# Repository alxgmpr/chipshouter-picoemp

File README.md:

# ChipSHOUTER-PicoEMP — Rev-2026

[![CC BY-SA 3.0][cc-by-sa-shield]][cc-by-sa]

A fork of [newaetech/chipshouter-picoemp](https://github.com/newaetech/chipshouter-picoemp)
adding **[`hardware/rev2026/`](hardware/rev2026/)** — a KiCad 10 port and rework
of the REV04 board. Upstream ships Altium sources and gerbers; this is an
editable KiCad project you can actually modify, with the design rules that matter
written down and enforced.

**[→ Rev-2026 documentation](hardware/rev2026/docs/)** &nbsp;·&nbsp;
[design notes](hardware/rev2026/docs/design-notes.md) &nbsp;·&nbsp;
[bring-up log](hardware/rev2026/docs/bringup.md) &nbsp;·&nbsp;
[open issues](hardware/rev2026/docs/open-issues.md) &nbsp;·&nbsp;
[fab outputs](hardware/rev2026/production/)

[Upstream's original README is preserved below.](#upstream-readme)

---

## What's different from REV04

* **Two upstream bugs fixed** — `R9` carried `R4`'s part data (75 Ω MPN on a 2 k
  part), and `C5` had no value.
* **A buffered trigger front-end** — a 74LVC1G17 Schmitt buffer with a series
  resistor and pulldown, plus an optional SMA input, instead of running the
  trigger straight into the Pico.
* **A bigger HV shield.** The 5.08 mm Phoenix terminal block is 13.80 mm tall and
  does not fit under upstream's 1551B half-shell, which gives 5.80 mm. This board
  uses an **inverted Hammond 1551G box** with 15.05 mm of clear height.
* **The 1 mm isolation barrier is enforced by a DRC rule** rather than by
  convention, with its reasoning and sources recorded in
  [`picoemp-rev2026.kicad_dru`](hardware/rev2026/picoemp-rev2026.kicad_dru).
* **All header footprints corrected** from 1.00/1.27 mm to 2.54 mm.

## Building one

1. **Boards** — upload
   [`hardware/rev2026/production/picoemp-rev2026-gerbers.zip`](hardware/rev2026/production/)
   to any fab. Two layers, 1.6 mm, 40.010 × 130.000 mm. The 1.6 mm thickness is
   required: the edge-mount SMA clamps the board edge and is specified for 0.062″.
2. **Parts** — [`production/bom.csv`](hardware/rev2026/production/) has MPNs,
   manufacturers and DigiKey part numbers for all 46 placed parts.
   [`bom/digikey-1board.txt`](hardware/rev2026/bom/) and `digikey-5boards.txt`
   are paste-ready DigiKey cart lists. **`R16` is DNP — do not fit it.**
3. **Shield** — Hammond 1551G, inverted, lid used as an underside cover on the
   same two #4 × ½″ screws. Trim `J4`'s pins to clear the lid's 3.05 mm recess.
4. **Firmware** — unchanged from upstream, in
   [`firmware/micropython/`](firmware/micropython/). This port does not modify it.
5. **Bring it up** — follow
   [`docs/bringup.md`](hardware/rev2026/docs/bringup.md), which is a real log
   from a real board rather than a checklist someone imagined.

**Read [`production/README.md`](hardware/rev2026/production/) and
[`docs/open-issues.md`](hardware/rev2026/docs/open-issues.md) before ordering.**
Nobody has fabbed from the current files yet — board #1 was built from an earlier
layout — and several known-imperfect items are not DRC violations, so no
automated check will catch them.

## Status

Both gates pass: 90 tests, and DRC reports 0 violations, 0 unconnected items and
0 schematic-parity issues. One board has been assembled and brought up: it
charges to roughly 261 V in about 2.1 seconds, asserts `CHARGED`, and discharges
on the button. **Pulsing has never been exercised** — there was no injection tip.

Two branches carry parked work that is not on `rev2026` and does not pass the
gates: [`feat/isolated-hv-sense`](../../tree/feat/isolated-hv-sense) (an AMC3336
block for calibrated isolated rail measurement) and
[`feat/hv-loop-return-plane`](../../tree/feat/hv-loop-return-plane) (a B.Cu
`HV_RTN` pour to cut discharge-loop inductance).

> ⚠️ **This is a high-voltage device.** It charges a capacitor to roughly 250 V,
> and the capacitor holds charge after power is removed. Everything in upstream's
> safety notes below applies to this board too — in particular, never operate it
> without the shield.

---

# Upstream README

Everything below is [NewAE's original README](https://github.com/newaetech/chipshouter-picoemp),
preserved unchanged. It describes the REV04 board that Rev-2026 is derived from,
and its safety guidance applies equally here.

The PicoEMP is a low-cost Electromagnetic Fault Injection (EMFI) tool, designed *specifically* for self-study and hobbiest research. Under the safety shield it looks like this:

You can see some details of the design in the [Intro Video](https://www.youtube.com/watch?v=nB5arJi-tVE).

## Thanks / Contributors

PicoEMP is a community-focused project, with major contributions from:
* Colin O'Flynn (original HW design, simple Python demo)
* [stacksmashing](https://twitter.com/ghidraninja) (C firmware for full PIO feature-set)
* [Lennert Wouters](https://twitter.com/LennertWo) (C improvements, first real demo)
* [@nilswiersma](https://github.com/nilswiersma) (Triggering/C improvements)

## Background

The [ChipSHOUTER](http://www.chipshouter.com) is a high-end Electromagnetic Fault Injection (EMFI) tool designed by Colin
at [NewAE Technology](http://www.newae.com). While not the first commercially available EMFI tool, ChipSHOUTER was the first
"easily purchasable" (even if expensive) tool with extensive open documentation. The tool was *not* open-source, but it
did contain a variety of detailed description of the design and architecture in the
[User Manual](https://github.com/newaetech/ChipSHOUTER/tree/master/documentation). The ChipSHOUTER design optimization focused in rough order on (1) safe operation, (2) high performance, (3) usability, and finally (4) cost. This results in a tool that covers many use-cases, but may be overkill (and too costly) for many. In additional, acquiring the safety testing/certification is not cheap, and must be accounted for in the product sale price.

The PicoEMP tries to fill in the gap that ChipSHOUTER leaves at the lower end of the spectrum. This PicoEMP project is *not* the
ChipSHOUTER. Instead it's designed to present a "bare bones" tool that has a design optimization focused in rough order of (1) safe
operation, (2) cost, (3) usability, (4) performance. Despite the focus on safety and low-cost, it works *suprisingly* well. It is also
*not* sold as a complete product - you are responsible for building it, ensuring it meets any relevant safety requirements/certifications,
and we completely disclaim all liability for what happens next. Please **only** use PicoEMP where you are building and controlling it
yourself, with total understanding of the operation and risks. It is *not* designed to be used in professional or educational environments,
where tools are expected to meet safety certifications (ChipSHOUTER was designed for these use-cases).

As an open-source project it also collects inputs from various community members, and welcomes your contributions! It also has various remixes of it, including:

* TODO link to people's remixes.

## Building a PicoEMP

The PicoEMP uses a Raspberry Pi Pico as the controller, inspired by @nezza using it for the debug-n-dump tool. You could alternatively use an Arduino or another microcontroller. You basically just need a few things:

1. PWM output to drive HV transformer.
2. Pulse pin to generate a pulse.
3. Status pin to monitor the HV status.

You have two options for building the PicoEMP: (1) total scratch build, or (2) easy-assemble build.

### Scratch Build

The PCB is *mostly* one layer. Original versions of it were milled on a Bantam PCB mill, and the final 'production' version is designed
to still allow this simple milling process. You can find details in the [gerbers](hardware/gerbers) folder, including Bantam-optimized files
which remove some of the smaller vias (used for the mounting holes), and require you to surface-mount the Raspberry Pi Pico. Here was
'rev3' of the PCB with a few hacked up tests:

If you've got time you can order the "real" PCBs from the [gerbers](hardware/gerbers) as well.

The BOM and build details are described in the [hardware](hardware) folder. If you cannot find the plastic shield (the upper half of Hammond
1551BTRD is used), you can find a simple 3D-printable shield as well. The official shield is low-cost and available from Digikey/Mouser/
Newark so you can purchase alongside everything else you need.

**IMPORTANT**: The plastic shield is critical for safe operation. While the output itself is isolated from the input connections, you will still **easily shock yourself** on the exposed high-voltage capacitor and circuitry. **NEVER** operate the device without the shield.

### Easy-Assemble Build

The Easy-Assembly build uses a "mostly complete" SMD board, which you need to solder a Raspberry Pi Pico, switches, and through-hole headers. Currently it's available only on the [NewAE Store](https://store.newae.com/chipshouter-picoemp). We're working to
get this listed on Mouser for much cheaper worldwide shipping (the NewAE store doesn't get great rates & due to issues with Canada's postal system for international shipments quotes mostly via DHL).

### Programming the PicoEMP

You'll need to program the PicoEMP with the firmware in the [firmware](firmware) directory. You can run other tasks on the microcontroller
as well.

### Building the EM Injection Tip (Probe / Coil)

You will also need an "injection tip", typically made with a ferrite core and some wires wrapped around it. You can see examples of such cores in the ChipSHOUTER kit. The following shows a few homemade & commercial tips:

You can make your own from suitable SMA connectors, magnet wire, and a ferrite core material. See the [injection_tips](hardware/injection_tips)
folder for more examples and details on building the probes.

*Reader Note: Please submit your own examples with a pull-request to this repo, it would be great to have more examples of probe geometries*

You can find additional examples of homemade cores in research papers such as:

* A. Cui, R. Housley, "BADFET: Defeating Modern Secure Boot Using Second-Order Pulsed Electromagnetic Fault Injection," USENIX Workshop on Offensive Technologies (WOOT 17), 2017.  [Paper Link.](https://www.usenix.org/conference/woot17/workshop-program/presentation/cui) [Slides Link.](https://github.com/RedBalloonShenanigans/BADFET)
* J. Balasch, D. Arumí and S. Manich, "Design and validation of a platform for electromagnetic fault injection," 2017 32nd Conference on Design of Circuits and Integrated Systems (DCIS), 2017, pp. 1-6. [Paper Link.](https://upcommons.upc.edu/bitstream/handle/2117/116688/bare_conf.pdf)
* J. Toulemont, G. Chancel, J. M. Galliere, F. Mailly, P. Nouet and P. Maurine, "On the scaling of EMFI probes," 2021 Workshop on Fault Detection and Tolerance in Cryptography (FDTC), 2021. [Paper Link.](https://ieeexplore.ieee.org/abstract/document/9565575) [Slides Link.](https://jaif.io/2021/media/JAIF2021%20-%20Toulemont.pdf)
* LimitedResults. "Enter the Gecko," 2021. [Blog Link](https://limitedresults.com/2021/06/enter-the-efm32-gecko/)
* C. Gaine, J-P. Nikolovski, D. Aboulkassimi, J-M. Dutertre. "New probe design for hardware characterization by ElectroMagnetic Fault Injection," EMC Europe 2022 [Paper Link.] (https://hal-cea.archives-ouvertes.fr/cea-03657852/file/article_archivesouvertes.pdf)
* 
### Useful References

If you don't know where to start with FI, you may find a couple chapters of the [Hardware Hacking Handbook](https://nostarch.com/hardwarehacking) useful.

You can see a demo of PicoEMP being used on a real attack in this [TI CC SimpleLink attack demo](https://github.com/KULeuven-COSIC/SimpleLink-FI/blob/main/notebooks/5_ChipSHOUTER-PicoEMP.ipynb).

## Using the PicoEMP

The general usage of the PicoEMP is as follows:

1. Press the "ARM" button. The red "ARMING" led will come on instantly telling you it's trying to charge the high voltage.
2. The red "HV" led will come on after a few seconds saying it is charged to "some voltage".
3. Place the probe tip overtop of the target.
4. Press the "Pulse" button.

You can see more examples of this in the [Intro Video](https://www.youtube.com/watch?v=nB5arJi-tVE).

You can even use the Raspberry Pi Pico to attack a Raspberry Pi "regular"! Here's a demo hitting a RSA signature on a Raspberry Pi (the demo code taken from Colin's [Remoticon 2021 Talk](https://github.com/colinoflynn/remoticon-2021-levelup-hardware-hacking/tree/master/rpi-glitching)):

**WARNING**: The high voltage will be applied across the SMA connector. If an injection tip (coil) is present, it will absorb most of the power. If you leave the SMA connector open, you will present a high voltage pulse across this SMA and could shock yourself. Do NOT touch the output SMA tip as a general "best practice", and treat the output as if it has a high voltage present.

The full ChipSHOUTER detects the missing connector tip and refuses to power up the high voltage, the PicoEMP does not have this failsafe!

## About the High Voltage Isolation

Most EMFI tools generate high voltages (similar to a camera flash). Many previous designs of open-source EMFI tools would work well, but [exposed the user to high voltages](https://github.com/RedBalloonShenanigans/BADFET). This was fine provided you use the tool correctly, but of course there is always a risk of grabbing the electrically "hot" tool! This common design choice happens because the easiest way to design an EMFI tool is with "low-side switching" (there is a very short mention of these design choices as well in my [book](https://www.nostarch.com/hardwarehacking) if you are curious). With low-side switching the output connector is always "hot", which presents a serious shock hazard.

PicoEMP gets around this problem by floating the high-voltage side, meaning there is no electrical path between the EMFI probe output and the input voltage ground. With the isolated high voltage output we can use the simple "low-side switching" in a safe manner. Some current will still flow due to the high-frequency spikes, so this isn't *perfect*, but it works well enough in practice (well enough you will shock yourself less often).

The caveat here is for this to work you also need to isolate your gate drive. There are a variety of [solutions to this](https://www.analog.com/en/technical-articles/powering-the-isolated-side-of-your-half-bridge-configuration.html), with the simplist being a gate drive transformer (GDT). The PicoEMP uses the transformer architecture, with some simplifications to further reduce BOM count.

More details of the design are available in the [hardware](hardware) folder.

### Hipot Testing for Validating Isolation

Easy-assemble builds have been subject to a hipot test. This test validates the isolation exists, and has not been compromised by things like leftover flux on the PCB.

This test applies a high voltage (1000V) from the SMA connector pads to the low-voltage signals shorted together. The test is done at 1000V DC, with test passing if LESS than 1 uA of current flows over the 60 seconds test duration. Note this limits is *far* lower than most industry standard limits.

### Technical Differences between ChipSHOUTER and PicoEMP

The main differences from a technical standpoint:

* ChipSHOUTER uses a much more powerful high voltage circuit and transformer (up to ~30W vs ~0.2W) that gives it
  almost unlimited glitch delivery, typically limited by your probe tip. The PicoEMP is slower to recover, typically ~1 to 4 seconds between
  glitches.

* ChipSHOUTER has a larger internal energy storage & more powerful output drivers.

* ChipSHOUTER has a controlled high-voltage setting from 150V to 500V. PicoEMP generates ~250V, there is some feedback but it's uncalibrated.
  **NOTE**: The PicoEMP allows some control of output pulse size by instead controlling the drive signal. This is less reliable (more variability
  in the output), but meets the goal of using the lowest-cost control method.

## License

This work is licensed under a [Creative Commons Attribution-ShareAlike 3.0 International License][cc-by-sa].

[cc-by-sa]: http://creativecommons.org/licenses/by-sa/3.0/
[cc-by-sa-image]: https://licensebuttons.net/l/by-sa/3.0/88x31.png
[cc-by-sa-shield]: https://img.shields.io/badge/License-CC%20BY--SA%203.0-lightgrey.svg

ChipSHOUTER is a trademark of NewAE Technology Inc., registered in the US, European Union, and other jurisdictions.
PicoEMP is a trademark of NewAE Technology Inc.

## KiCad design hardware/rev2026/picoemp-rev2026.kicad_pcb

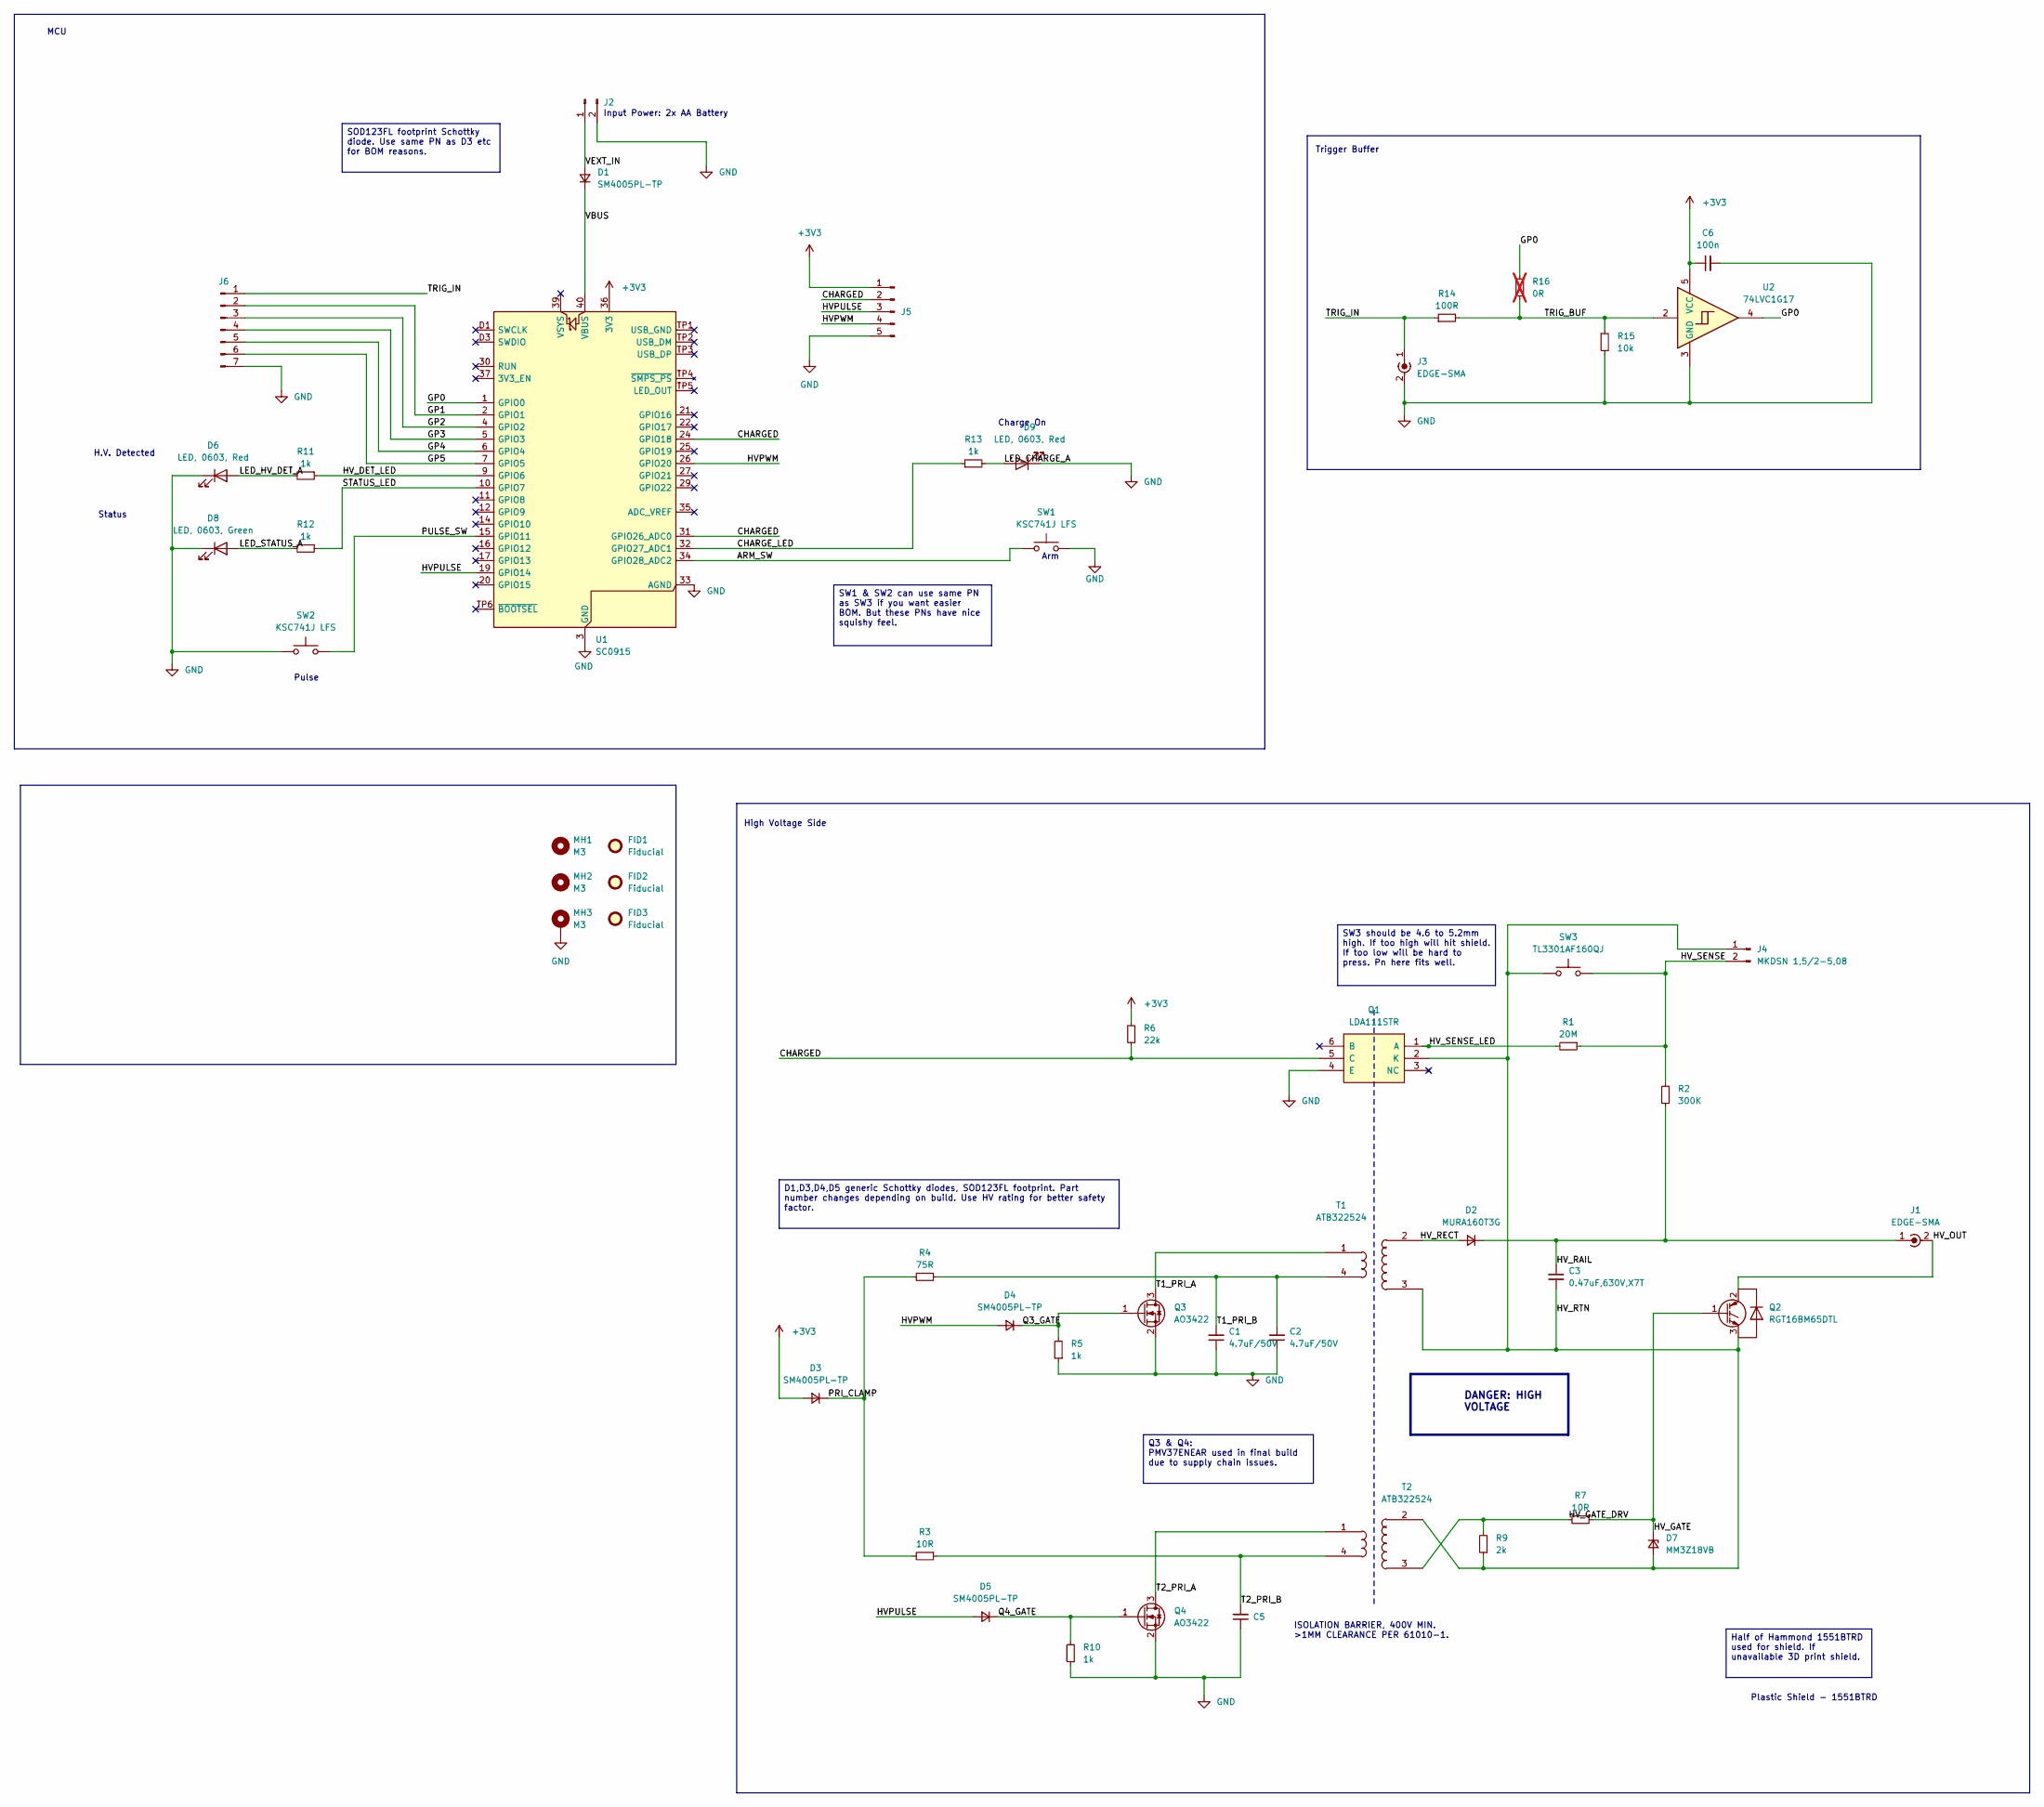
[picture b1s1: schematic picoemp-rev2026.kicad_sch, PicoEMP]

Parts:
C1, C2: 4.7uF/50V; C_0805_2012Metric; MPN C2012X5R1H475K125AB; DigiKey 445-5980-1-ND
C3: 0.47uF,630V,X7T; C_2220_5750Metric; MPN GR355DD7LQ474KW01K; DigiKey 490-GR355DD7LQ474KW01KCT-ND
C5, C6: 100n; C_0603_1608Metric; MPN C0603C104K5RACTU; DigiKey 399-5089-2-ND
D1, D3, D4, D5: SM4005PL-TP; D_SOD-123FL; MPN SM4005PL-TP; DigiKey SM4005PL-TPMSCT-ND
D2: MURA160T3G; D_SMA; MPN MURA160T3G
D6, D9: LED, 0603, Red; LED_0603_1608Metric; MPN APT1608SURCK; DigiKey 754-1123-1-ND
D7: MM3Z18VB; D_SOD-323F; MPN MM3Z18VB; DigiKey MM3Z18VBCT-ND
D8: LED, 0603, Green; LED_0603_1608Metric; MPN APT1608CGCK; DigiKey 754-1116-1-ND
FID1, FID2, FID3: Fiducial; Fiducial_0.5mm_Mask1.5mm
J1, J3: EDGE-SMA; SMA_Linx_CONSMA020_062_G_EdgeMount; MPN CONSMA020.062-G; DigiKey 343-CONSMA020.062-G-ND
J2: 1x2_Pin_Header; JST_XH_S2B-XH-A_1x02_P2.50mm_Horizontal; MPN S2B-XH-A(LF)(SN); DigiKey 455-2257-ND
J4: MKDSN 1,5/2-5,08; TerminalBlock_Phoenix_MKDSN-1,5-2-5.08_1x02_P5.08mm_Horizon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; MPN 1548128
J5: Header 5; PinHeader_1x05_P2.54mm_Vertical
J6: Header 7; PinHeader_1x07_P2.54mm_Vertical
MH1, MH2: M3; MountingHole_3.2mm_M3
MH3: M3; MountingHole_3.2mm_M3_Pad_Via
Q1: LDA111STR; SOP-6_LDA111; MPN LDA111STR; DigiKey 212-LDA111SCT-ND
Q2: RGT16BM65DTL; TO-252-3_TabPin2; MPN RGT16BM65DTL
Q3, Q4: AO3422; SOT-23; MPN AO3422
R1: 20M; R_2010_5025Metric; MPN CRMA2010AF20M0FKEF
R2: 300K; R_2512_6332Metric; MPN 3522300KFT; DigiKey A121215CT-ND
R3, R7: 10R; R_0603_1608Metric; MPN RC0603FR-0710RL; DigiKey 311-10.0HRCT-ND
R4: 75R; R_0805_2012Metric; MPN RC0805FR-0775RL; DigiKey 311-75.0CRCT-ND
R5, R10, R11, R12, R13: 1k; R_0603_1608Metric; MPN RC0603FR-071KL; DigiKey 311-1.00KHRCT-ND
R6: 22k; R_0603_1608Metric; MPN RC0603FR-0722KL; DigiKey 311-22.0KHRCT-ND
R9: 2k; R_0805_2012Metric; MPN RC0805FR-072KL; DigiKey 311-2.00KCRCT-ND
R14: 100R; R_0603_1608Metric; MPN RC0603FR-07100RL; DigiKey 311-100HRCT-ND
R15: 10k; R_0603_1608Metric; MPN RC0603FR-0710KL; DigiKey 311-10.0KHRCT-ND
R16: 0R; R_0603_1608Metric; MPN RC0603JR-070RL; DigiKey 311-0.0GRCT-ND; not fitted
SW1, SW2: KSC741J LFS; SW_Push_1P1T_NO_CK_KSC7xxJ; MPN KSC741JLFS; DigiKey CKN10309CT-ND
SW3: TL3301AF160QJ; SW_Push_ESwitch_TL3301AJ; MPN TL3301AF160QJ; DigiKey EG4374CT-ND
T1, T2: ATB322524; MPN ATB322524-0110-T000; DigiKey 445-8636-1-ND
U1: SC0915; RaspberryPi_Pico_SMD; MPN SC0915
U2: 74LVC1G17; SOT-23-5; MPN 74LVC1G17GV,125; DigiKey 1727-6070-1-ND

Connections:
+3V3: C6.1, D3.2 (A), J5.1, R6.2, U1.36 (3V3), U2.5 (VCC)
/ARM_SW: SW1.1, U1.34 (GPIO28_ADC2)
/CHARGED: J5.2, Q1.5 (C), R6.1, U1.24 (GPIO18), U1.31 (GPIO26_ADC0)
/CHARGE_LED: R13.1, U1.32 (GPIO27_ADC1)
/GP0: R16.1, U1.1 (GPIO0), U2.4
/GP1: J6.2, U1.2 (GPIO1)
/GP2: J6.3, U1.4 (GPIO2)
/GP3: J6.4, U1.5 (GPIO3)
/GP4: J6.5, U1.6 (GPIO4)
/GP5: J6.6, U1.7 (GPIO5)
/HVPULSE: D5.2 (A), J5.3, U1.19 (GPIO14)
/HVPWM: D4.2 (A), J5.4, U1.26 (GPIO20)
/HV_DET_LED: R11.1, U1.9 (GPIO6)
/HV_GATE: D7.1 (K), Q2.1 (G), R7.1
/HV_GATE_DRV: R7.2, R9.2, T2.3
/HV_OUT: J1.2 (Ext), Q2.2 (C)
/HV_RAIL: C3.2, D2.1 (K), J1.1 (In), R2.1
/HV_RECT: D2.2 (A), T1.2
/HV_RTN: C3.1, D7.2 (A), J4.1, Q1.2 (K), Q2.3 (E), R9.1, SW3.1, T1.3, T2.2
/HV_SENSE: J4.2, R1.1, R2.2, SW3.2
/HV_SENSE_LED: Q1.1 (A), R1.2
/LED_CHARGE_A: D9.2 (A), R13.2
/LED_HV_DET_A: D6.2 (A), R11.2
/LED_STATUS_A: D8.2 (A), R12.2
/PRI_CLAMP: D3.1 (K), R3.2, R4.2
/PULSE_SW: SW2.1, U1.15 (GPIO11)
/Q3_GATE: D4.1 (K), Q3.1 (G), R5.2
/Q4_GATE: D5.1 (K), Q4.1 (G), R10.2
/STATUS_LED: R12.1, U1.10 (GPIO7)
/T1_PRI_A: Q3.3 (D), T1.1
/T1_PRI_B: C1.2, C2.2, R4.1, T1.4
/T2_PRI_A: Q4.3 (D), T2.1
/T2_PRI_B: C5.2, R3.1, T2.4
/TRIG_BUF: R14.2, R15.1, R16.2, U2.2
/TRIG_IN: J3.1 (In), J6.1, R14.1
/VBUS: D1.1 (K), U1.40 (VBUS)
/VEXT_IN: D1.2 (A), J2.1
GND: C1.1, C2.1, C5.1, C6.2, D6.1 (K), D8.1 (K), D9.1 (K), J2.2, J3.2 (Ext), J5.5, J6.7, MH3.1 (1_1), Q1.4 (E), Q3.2 (S), Q4.2 (S), R5.1, R10.1, R15.2, SW1.2, SW2.2, U1.3 (GND), U1.8 (GND), U1.13 (GND), U1.18 (GND), U1.23 (GND), U1.28 (GND), U1.33 (AGND), U1.38 (GND), U1.D2 (GND), U2.3 (GND)

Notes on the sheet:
MCU
High Voltage Side
Plastic Shield - 1551BTRD‎
Pulse
Charge On
H.V. Detected
Arm
Input Power: 2x AA Battery
Trigger Buffer
ISOLATION BARRIER, 400V MIN. >1MM CLEARANCE PER 61010-1.
Q3 & Q4: PMV37ENEAR used in final build due to supply chain issues.
SW3 should be 4.6 to 5.2mm high. If too high will hit shield. If too low will be hard to press. Pn here fits well.
Half of Hammond 1551BTRD used for shield. If unavailable 3D print shield.
Status
SOD123FL footprint Schottky diode. Use same PN as D3 etc for BOM reasons.
SW1 & SW2 can use same PN as SW3 if you want easier BOM. But these PNs have nice squishy feel.
DANGER: HIGH VOLTAGE
D1,D3,D4,D5 generic Schottky diodes, SOD123FL footprint. Part number changes depending on build. Use HV rating for better safety factor.

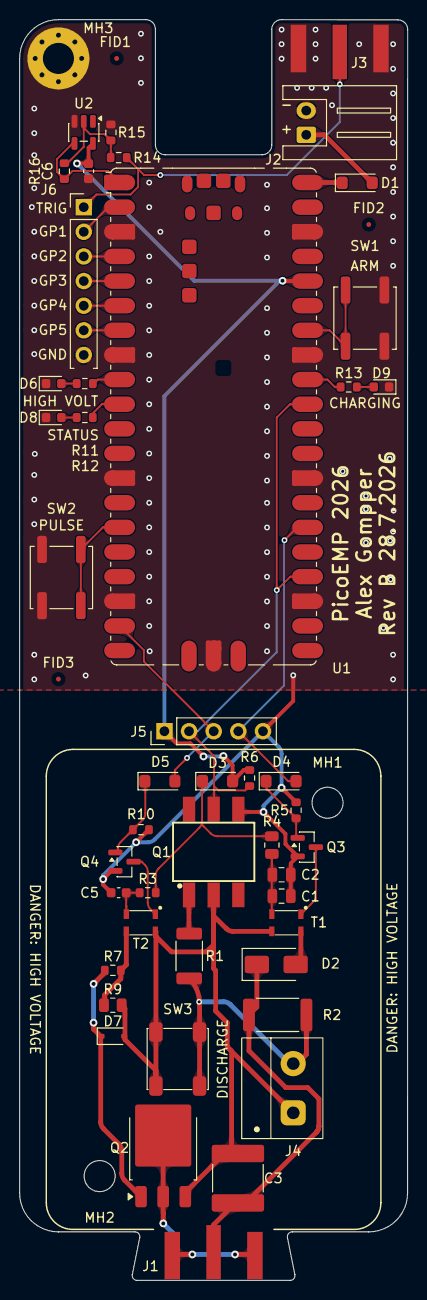
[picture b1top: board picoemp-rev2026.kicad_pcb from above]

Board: 2 copper layers, 40.0 x 130.0 mm, 52 parts (0 on the bottom side), 38 nets.

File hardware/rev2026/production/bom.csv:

"Refs","Value","Footprint","MPN","Manufacturer","DigiKey","DNP","Qty"
"C1,C2","4.7uF/50V","Capacitor_SMD:C_0805_2012Metric","C2012X5R1H475K125AB","TDK","445-5980-1-ND","","2"
"C3","0.47uF,630V,X7T","Capacitor_SMD:C_2220_5750Metric","GR355DD7LQ474KW01K","Murata Electronics","490-GR355DD7LQ474KW01KCT-ND","","1"
"C5,C6","100n","Capacitor_SMD:C_0603_1608Metric","C0603C104K5RACTU","KEMET","399-5089-2-ND","","2"
"D1,D3-D5","SM4005PL-TP","picoemp:D_SOD-123FL","SM4005PL-TP","MCC","SM4005PL-TPMSCT-ND","","4"
"D2","MURA160T3G","Diode_SMD:D_SMA","MURA160T3G","onsemi","","","1"
"D6,D9","LED, 0603, Red","LED_SMD:LED_0603_1608Metric","APT1608SURCK","Kingbright","754-1123-1-ND","","2"
"D7","MM3Z18VB","Diode_SMD:D_SOD-323F","MM3Z18VB","onsemi","MM3Z18VBCT-ND","","1"
"D8","LED, 0603, Green","LED_SMD:LED_0603_1608Metric","APT1608CGCK","Kingbright","754-1116-1-ND","","1"
"J1,J3","EDGE-SMA","picoemp:SMA_Linx_CONSMA020_062_G_EdgeMount","CONSMA020.062-G","TE Connectivity Linx","343-CONSMA020.062-G-ND","","2"
"J2","1x2_Pin_Header","Connector_JST:JST_XH_S2B-XH-A_1x02_P2.50mm_Horizontal","S2B-XH-A(LF)(SN)","JST","455-2257-ND","","1"
"J4","MKDSN 1,5/2-5,08","picoemp:TerminalBlock_Phoenix_MKDSN-1,5-2-5.08_1x02_P5.08mm_Horizontal","1548128","Phoenix Contact","","","1"
"J5","Header 5","Connector_PinHeader_2.54mm:PinHeader_1x05_P2.54mm_Vertical","","","","","1"
"J6","Header 7","Connector_PinHeader_2.54mm:PinHeader_1x07_P2.54mm_Vertical","","","","","1"
"Q1","LDA111STR","picoemp:SOP-6_LDA111","LDA111STR","IXYS SEMICONDUCTOR","212-LDA111SCT-ND","","1"
"Q2","RGT16BM65DTL","Package_TO_SOT_SMD:TO-252-3_TabPin2","RGT16BM65DTL","ROHM","","","1"
"Q3,Q4","AO3422","Package_TO_SOT_SMD:SOT-23","AO3422","Alpha & Omega Semiconductor","","","2"
"R1","20M","Resistor_SMD:R_2010_5025Metric","CRMA2010AF20M0FKEF","Vishay","","","1"
"R2","300K","Resistor_SMD:R_2512_6332Metric","3522300KFT","TE Connectivity","A121215CT-ND","","1"
"R3,R7","10R","Resistor_SMD:R_0603_1608Metric","RC0603FR-0710RL","Yageo","311-10.0HRCT-ND","","2"
"R4","75R","Resistor_SMD:R_0805_2012Metric","RC0805FR-0775RL","Yageo","311-75.0CRCT-ND","","1"
"R5,R10-R13","1k","Resistor_SMD:R_0603_1608Metric","RC0603FR-071KL","Yageo","311-1.00KHRCT-ND","","5"
"R6","22k","Resistor_SMD:R_0603_1608Metric","RC0603FR-0722KL","Yageo","311-22.0KHRCT-ND","","1"
"R9","2k","Resistor_SMD:R_0805_2012Metric","RC0805FR-072KL","Yageo","311-2.00KCRCT-ND","","1"
"R14","100R","Resistor_SMD:R_0603_1608Metric","RC0603FR-07100RL","Yageo","311-100HRCT-ND","","1"
"R15","10k","Resistor_SMD:R_0603_1608Metric","RC0603FR-0710KL","Yageo","311-10.0KHRCT-ND","","1"
"R16","0R","Resistor_SMD:R_0603_1608Metric","RC0603JR-070RL","Yageo","311-0.0GRCT-ND","DNP","1"
"SW1,SW2","KSC741J LFS","Button_Switch_SMD:SW_Push_1P1T_NO_CK_KSC7xxJ","KSC741JLFS","C&K","CKN10309CT-ND","","2"
"SW3","TL3301AF160QJ","picoemp:SW_Push_ESwitch_TL3301AJ","TL3301AF160QJ","E-Switch","EG4374CT-ND","","1"
"T1,T2","ATB322524","picoemp:ATB322524","ATB322524-0110-T000","TDK","445-8636-1-ND","","2"
"U1","SC0915","Module:RaspberryPi_Pico_SMD","SC0915","Raspberry Pi","","","1"
"U2","74LVC1G17","Package_TO_SOT_SMD:SOT-23-5","74LVC1G17GV,125","Nexperia","1727-6070-1-ND","","1"

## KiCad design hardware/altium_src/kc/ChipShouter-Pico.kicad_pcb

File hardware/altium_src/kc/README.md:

# ⚠️ Incomplete REV04 → KiCad migration — do not use as a reference

This directory is an **abandoned, in-progress** import of the upstream REV04
Altium design into KiCad. It is kept for history only.

**It has at least one known wiring error.** In the HV sense section, `R1`'s
lower lead lands on `HV_RTN` and `Q1` pin 1 floats, because the Altium import
flattened a wire hop into a junction. The sense chain is therefore wrong.

Its `audit/AUDIT.md` §4b also states the sense chain as "HV → R1 → Q1 LED → R2 →
GND". That is wrong too — the real order puts `R2` first.

## Where to look instead

| For | Use |
|---|---|
| **Ground truth on circuit topology** | [`../../SCH-PICOEMP-REV04.PDF`](../../SCH-PICOEMP-REV04.PDF) |
| A working KiCad version of this board | [`../../rev2026/`](../../rev2026/) |
| The original Altium sources | [`../`](../) |

The correct sense chain is:

```
HV_RAIL → R2 (300K) → HV_SENSE → R1 (20M) → Q1 LED → HV_RTN
```

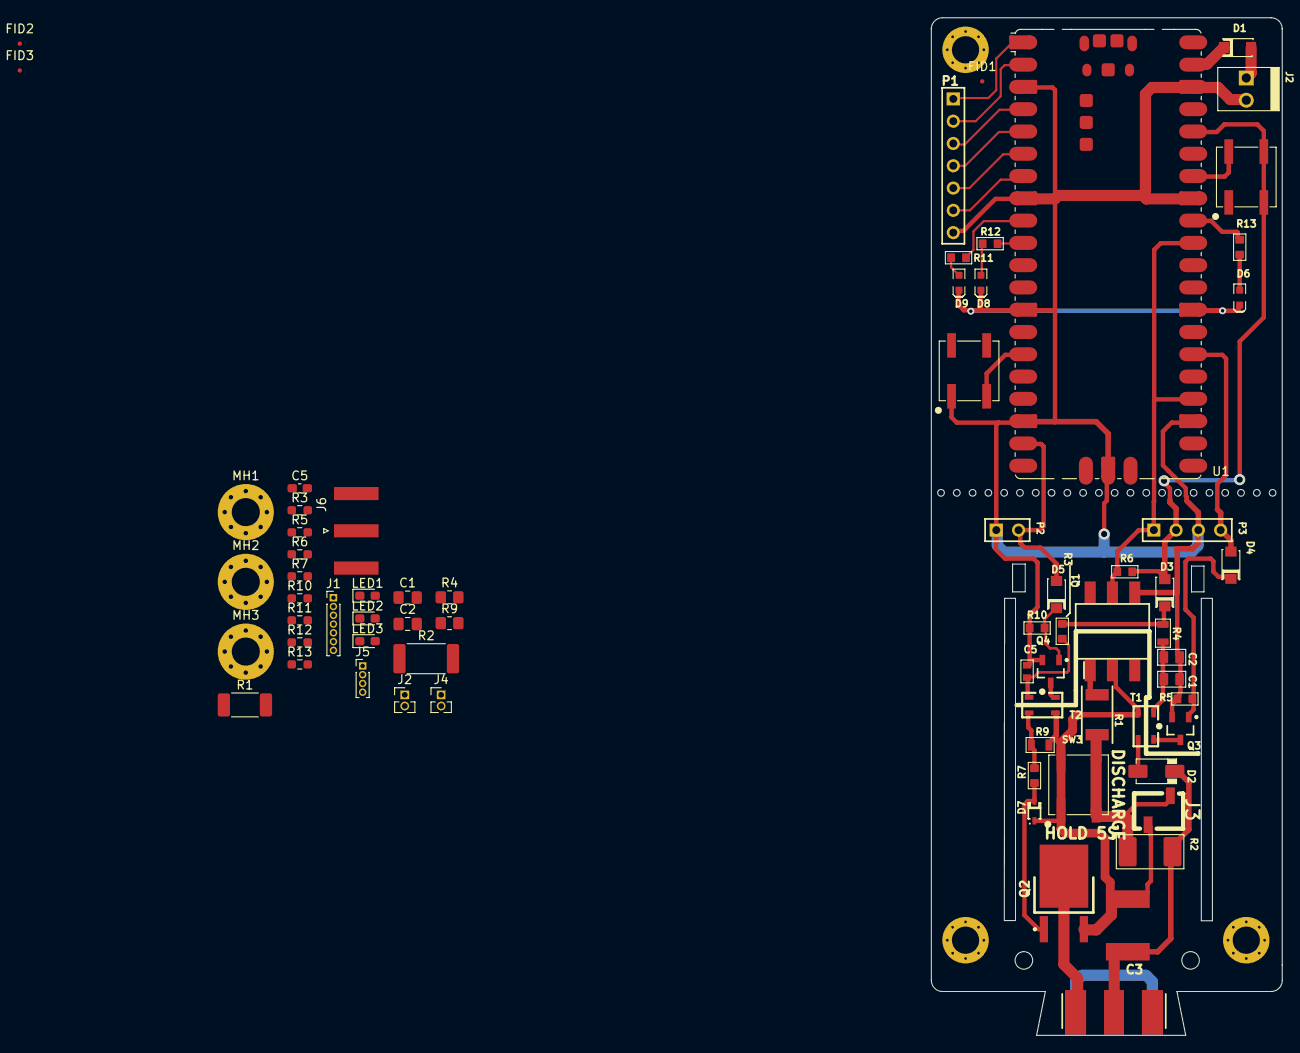
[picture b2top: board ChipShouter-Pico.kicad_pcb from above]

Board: 2 copper layers, 40.0 x 116.0 mm, 73 parts (0 on the bottom side), 47 nets.

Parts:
C1, C2: 4.7uF/50V; C_0805_2012Metric_Pad1.18x1.45mm_HandSolder
C1#2, C2#2: 4.7uF/50V; CAPC0805_M
C3: 0.47uF,630V,X7T; CKG57N_2220
C5: ${ALTIUM_VALUE}; C_0603_1608Metric_Pad1.08x0.95mm_HandSolder
C5#2: 100n; CAPC0603_M
D1, D3, D4, D5: DSS13UTR
D2: MURA160T3G; DO-214AC
D6, D9: LED, 0603, Red; LED-0603-RED
D7: MM3Z18VB; SOD323
D8: LED, 0603, Green; LED-0603-GREEN
FID1, FID2, FID3: Fiducial; Fiducial_0.5mm_Mask1.5mm
J1: Header 7; PinHeader_1x07_P1.00mm_Vertical
J1#2: EDGE-SMA; CON-SMA-MALE-PCB-EDGE062
J2: 1x2_Pin_Header; PinHeader_1x02_P1.27mm_Vertical
J2#2: 1x2_Pin_Header; 22-23-2021
J3: BG306-02-A-2-0400-L-G; BG306-R2-2PIN
J4: Header 2; PinHeader_1x02_P1.27mm_Vertical
J5: Header 4; PinHeader_1x04_P1.00mm_Vertical
J6: EDGE-SMA; SMA_Amphenol_132289_EdgeMount
LED1, LED3: LED, 0603, Red; LED_0603_1608Metric_Pad1.05x0.95mm_HandSolder
LED2: LED, 0603, Green; LED_0603_1608Metric_Pad1.05x0.95mm_HandSolder
MH1, MH2, MH3#2: M3; MountingHole_3.2mm_M3_Pad_Via
MH1#2, MH2#2, MH3: M3, Tight Fit; MOUNT_M3_TIGHT
P1: Header 7; HDR1X7
P2: Header 2; HDR1X2
P3: Header 4; HDR1X4
Q1: LDA111STR; SOP254P952X470-6N
Q2: RGT16BM65DTL; DPAK_TO-252AA_M
Q3, Q4: AO3422; SOT95P245X110-3M
R1: 20M; R_2010_5025Metric_Pad1.40x2.65mm_HandSolder
R1#2: 20M; RESC5025X06N
R2: 300K; RESC6432X06N
R2#2: 300K; R_2512_6332Metric_Pad1.40x3.35mm_HandSolder
R3, R7: 10R; R_0603_1608Metric_Pad0.98x0.95mm_HandSolder
R3#2, R7#2: 10R; RESC1608X55N
R4: 75R; RESC2012X70N
R4#2: 75R; R_0805_2012Metric_Pad1.20x1.40mm_HandSolder
R5, R10, R11#2, R12, R13: 1k; RESC1608X55N
R5#2, R10#2, R11, R12#2, R13#2: 1k; R_0603_1608Metric_Pad0.98x0.95mm_HandSolder
R6: 22k; RESC1608X55N
R6#2: 22k; R_0603_1608Metric_Pad0.98x0.95mm_HandSolder
R9: 2k; RESC2012X70N
R9#2: 2k; R_0805_2012Metric_Pad1.20x1.40mm_HandSolder
SW1, SW2, SW3: KSC741J LFS; CK_KSC7J
T1, T2: ATB322524
U1: SC0915; RaspberryPi_Pico_SMD

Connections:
+3V3: J5.2, R6#2.2, U1.36 (3V3)
/CHARGED: J5.1, R6#2.1, U1.24 (GPIO18), U1.31 (GPIO26_ADC0)
/HVPULSE: J4.2, U1.19 (GPIO14)
/HVPWM: J5.4, U1.26 (GPIO20)
CHARGED: P3.1, Q1.5, R6.2
GND: C1.1, C1#2.2, C2.1, C2#2.2, C5.1, C5#2.2, D6.K, D8.K, D9.K, J1.7, J2.2, J2#2.2, J4.1, J5.3, LED1.1 (K), LED2.1 (K), LED3.1 (K), P1.7, P2.1, P3.3, Q1.4, Q3.2, Q4.2, R5.2, R5#2.1, R10.2, R10#2.1, SW2.1, U1.3 (GND), U1.8 (GND), U1.13 (GND), U1.18 (GND), U1.23 (GND), U1.28 (GND), U1.33 (AGND), U1.38 (GND), U1.D2 (GND)
HVPULSE: D5.A, P2.2
HVPWM: D4.A, P3.4
unnamed: C1.2, C2.2, R4#2.1
unnamed: C5.2, R3.1
unnamed: J6.1 (In), R2#2.1
unnamed: R3.2, R4#2.2
unnamed: R1.2, R9#2.1
unnamed: J1.1, U1.1 (GPIO0)
unnamed: J1.2, U1.2 (GPIO1)
unnamed: J1.3, U1.4 (GPIO2)
unnamed: J1.4, U1.5 (GPIO3)
unnamed: J1.5, U1.6 (GPIO4)
unnamed: J1.6, U1.7 (GPIO5)
unnamed: R1.1, R2#2.2
unnamed: LED1.2 (A), R11.2
unnamed: LED2.2 (A), R12#2.2
unnamed: LED3.2 (A), R13#2.2
unnamed: R7.2, R9#2.2
unnamed: R11.1, U1.9 (GPIO6)
unnamed: R12#2.1, U1.10 (GPIO7)
unnamed: R13#2.1, U1.32 (GPIO27_ADC1)
NetC1_1: C1#2.1, C2#2.1, R4.2, T1.4
NetC3_1: C3.1, D2.K, J1#2.1, R2.2
NetC3_2: C3.2, D7.A, J3.1, Q1.2, Q2.2, R9.2, SW3.1, SW3.4, T1.3, T2.2
NetC5_1: C5#2.1, R3#2.2, T2.4
NetD1_A: D1.A, J2#2.1
NetD2_A: D2.A, T1.2
NetD3_K: D3.K, R3#2.1, R4.1
NetD4_K: D4.K, Q3.1, R5.1
NetD5_K: D5.K, Q4.1, R10.1
NetD6_A: D6.A, R13.1
NetD7_K: D7.K, Q2.1, R7#2.2
NetD8_A: D8.A, R12.1
NetD9_A: D9.A, R11#2.1
NetJ1_2: J1#2.2, J1#2.3, J1#2.4, J1#2.5, Q2.3
NetJ3_2: J3.2, R1#2.2, R2.1, SW3.2, SW3.3
NetQ1_1: Q1.1, R1#2.1
NetQ3_3: Q3.3, T1.1
NetQ4_3: Q4.3, T2.1
NetR7_1: R7#2.1, R9.1, T2.3
VCC: D3.A, P3.2, R6.1, SW1.2, SW1.3

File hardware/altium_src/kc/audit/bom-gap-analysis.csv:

Ref,Sch Value,ALTIUM_VALUE,Upstream Desc,Upstream MPN,Upstream Mfr,Sch MPN,Internal PN,Footprint,FP Status,Symbol lib_id,Sym Status,Issues
C1,4.7uF/50V,,4.7uF 50V 0805,C2012X5R1H475K125AB,TDK,,,Capacitor_SMD:C_0805_2012Metric_Pad1.18x1.45mm_HandSolder,OK,Device:C_Small,OK,
C2,4.7uF/50V,,4.7uF 50V 0805,C2012X5R1H475K125AB,TDK,,,Capacitor_SMD:C_0805_2012Metric_Pad1.18x1.45mm_HandSolder,OK,Device:C_Small,OK,
C3,"0.47uF,630V,X7T",,0.47uF 630V X7T 2220,KRM55TR72J474MH01K,Murata,,,CKG57N_2220,UNRESOLVABLE,Device:C_Small,OK,footprint unresolvable ((no lib prefix))
C5,${ALTIUM_VALUE},,100nF 0603,C0603C104K5RACTU,KEMET,,,Capacitor_SMD:C_0603_1608Metric_Pad1.08x0.95mm_HandSolder,OK,Device:C_Small,OK,VALUE RENDERS LITERALLY
D1,SM4005PL-TP,,600V 1A rectifier,SM4005PL-TP,MCC,,,,MISSING,Device:D_Schottky_Small,OK,footprint missing ((none))
D2,MURA160T3G,,600V 1A fast recovery,MURA160T3G,onsemi,,,SMA,UNRESOLVABLE,Device:D_Small,OK,footprint unresolvable ((no lib prefix))
D3,SM4005PL-TP,,600V 1A rectifier,SM4005PL-TP,MCC,,,DSS13UTR,UNRESOLVABLE,Device:D_Schottky_Small,OK,footprint unresolvable ((no lib prefix))
D4,SM4005PL-TP,,600V 1A rectifier,SM4005PL-TP,MCC,,,DSS13UTR,UNRESOLVABLE,Device:D_Schottky_Small,OK,footprint unresolvable ((no lib prefix))
D5,SM4005PL-TP,,600V 1A rectifier,SM4005PL-TP,MCC,,,DSS13UTR,UNRESOLVABLE,Device:D_Schottky_Small,OK,footprint unresolvable ((no lib prefix))
D7,MM3Z18VB,,18V zener SOD-323,MM3Z18VB,onsemi,,,SOD323,UNRESOLVABLE,Device:D_Zener_Small,OK,footprint unresolvable ((no lib prefix))
J1,Header 7,,1x7 hdr 2.54mm,-,-,,,Connector_PinHeader_1.00mm:PinHeader_1x07_P1.00mm_Vertical,OK,Connector:Conn_01x07_Pin,OK,DNP; excluded from BOM
J2,1x2_Pin_Header,,JST XH 2-pin THT,S2B-XH-A(LF)(SN),JST,22-23-2021n22-23-2021,Molex_2_Pin,Connector_PinHeader_1.27mm:PinHeader_1x02_P1.27mm_Vertical,OK,Connector:Conn_01x02_Pin,OK,MPN MISMATCH vs upstream (22-23-2021n22-23-2021 vs S2B-XH-A(LF)(SN)); DNP; excluded from BOM
J3,BG306-02-A-2-0400-L-G,,2-pin SMD hdr (HV cal),BG306-02-A-2-0400-L-G,GCT,,,,MISSING,Connector:Conn_01x02_Pin,OK,footprint missing ((none)); DNP; excluded from BOM
J4,Header 2,,1x2 hdr 2.54mm,-,-,,,Connector_PinHeader_1.27mm:PinHeader_1x02_P1.27mm_Vertical,OK,Connector:Conn_01x02_Pin,OK,DNP; excluded from BOM
J5,Header 4,,1x4 hdr 2.54mm,-,-,,,Connector_PinHeader_1.00mm:PinHeader_1x04_P1.00mm_Vertical,OK,Connector:Conn_01x04_Pin,OK,DNP; excluded from BOM
J6,EDGE-SMA,,Edge-mount SMA,0732511150 / 142-0701-801,Molex / Cinch,,,Connector_Coaxial:SMA_Amphenol_132289_EdgeMount,OK,Connector:Conn_Coaxial_Power,OK,
LED1,"LED, 0603, Red",,Red 0603 LED,APT1608SRCPRV,Kingbright,,,LED_SMD:LED_0603_1608Metric_Pad1.05x0.95mm_HandSolder,OK,Device:LED,OK,
LED2,"LED, 0603, Green",,Green 0603 LED,APT1608CGCK,Kingbright,,,LED_SMD:LED_0603_1608Metric_Pad1.05x0.95mm_HandSolder,OK,Device:LED,OK,
LED3,"LED, 0603, Red",,Red 0603 LED,APT1608SRCPRV,Kingbright,,,LED_SMD:LED_0603_1608Metric_Pad1.05x0.95mm_HandSolder,OK,Device:LED,OK,
Q1,LDA111STR,,Low-current opto,LDA111STR,IXYS,LDA111STR,,C__Users_colin_Documents_AltiumLL_SamacSys.PcbLib:SOP254P952X470-6N,UNRESOLVABLE,*:root_0_mirrored_LDA111STR_*,UNRESOLVABLE,footprint unresolvable (C__Users_colin_Documents_AltiumLL_SamacSys.PcbLib); symbol lib unresolvable (*:root_0_mirrored_LDA111STR_*)
Q2,RGT16BM65DTL,,IGBT 650V DPAK,RGT16BM65DTL,Rohm,,,,MISSING,Device:Q_NMOS_Depletion,OK,footprint missing ((none))
Q3,AO3422,,NMOS 30V SOT-23,AO3422,AOS,,,,MISSING,Device:Q_NMOS_Depletion,OK,footprint missing ((none))
Q4,AO3422,,NMOS 30V SOT-23,AO3422,AOS,,,,MISSING,Device:Q_NMOS_Depletion,OK,footprint missing ((none))
R1,${ALTIUM_VALUE},20M,20M 2010 1%,CRMA2010AF20M0FKEF,Vishay,CRMA2010AF20M0FKEF,RCHIP-20M-2010,Resistor_SMD:R_2010_5025Metric_Pad1.40x2.65mm_HandSolder,OK,Device:R_Small,OK,"value is a variable ref, not flattened"
R2,${ALTIUM_VALUE},300K,300K 2512 3W,3522300KFT,TE/CGS,3522300KFT,RCHIP-300K-2512,Resistor_SMD:R_2512_6332Metric_Pad1.40x3.35mm_HandSolder,OK,Device:R_Small,OK,"value is a variable ref, not flattened"
R3,${ALTIUM_VALUE},10R,10R 0603,RC0603FR-0710RL,Yageo,RC0603FR-0710RL,RCHIP-10R-0603,Resistor_SMD:R_0603_1608Metric_Pad0.98x0.95mm_HandSolder,OK,Device:R_Small,OK,"value is a variable ref, not flattened"
R4,75R,75R,75R 0805,RC0805FR-0775RL,Yageo,RC0805FR-0775RL,RCHIP-75R-0805,Resistor_SMD:R_0805_2012Metric_Pad1.20x1.40mm_HandSolder,OK,Device:R_Small,OK,
R5,${ALTIUM_VALUE},1k,1k 0603,RC0603FR-071KL,Yageo,RC0603FR-071KL,RCHIP-1K-0603,Resistor_SMD:R_0603_1608Metric_Pad0.98x0.95mm_HandSolder,OK,Device:R_Small,OK,"value is a variable ref, not flattened"
R6,${ALTIUM_VALUE},22k,22k 0603,RC0603FR-0722KL,Yageo,RC0603FR-0722KL,RCHIP-22K-0603,Resistor_SMD:R_0603_1608Metric_Pad0.98x0.95mm_HandSolder,OK,Device:R_Small,OK,"value is a variable ref, not flattened"
R7,${ALTIUM_VALUE},10R,10R 0603,RC0603FR-0710RL,Yageo,RC0603FR-0710RL,RCHIP-10R-0603,Resistor_SMD:R_0603_1608Metric_Pad0.98x0.95mm_HandSolder,OK,Device:R_Small,OK,"value is a variable ref, not flattened"
R9,2k,75R,2k 0805,RC0805FR-072KL,Yageo,RC0805FR-0775RL,RCHIP-75R-0805,Resistor_SMD:R_0805_2012Metric_Pad1.20x1.40mm_HandSolder,OK,Device:R_Small,OK,MPN MISMATCH vs upstream (RC0805FR-0775RL vs RC0805FR-072KL)
R10,${ALTIUM_VALUE},1k,1k 0603,RC0603FR-071KL,Yageo,RC0603FR-071KL,RCHIP-1K-0603,Resistor_SMD:R_0603_1608Metric_Pad0.98x0.95mm_HandSolder,OK,Device:R_Small,OK,"value is a variable ref, not flattened"
R11,${ALTIUM_VALUE},1k,1k 0603,RC0603FR-071KL,Yageo,RC0603FR-071KL,RCHIP-1K-0603,Resistor_SMD:R_0603_1608Metric_Pad0.98x0.95mm_HandSolder,OK,Device:R_Small,OK,"value is a variable ref, not flattened"
R12,${ALTIUM_VALUE},1k,1k 0603,RC0603FR-071KL,Yageo,RC0603FR-071KL,RCHIP-1K-0603,Resistor_SMD:R_0603_1608Metric_Pad0.98x0.95mm_HandSolder,OK,Device:R_Small,OK,"value is a variable ref, not flattened"
R13,${ALTIUM_VALUE},1k,1k 0603,RC0603FR-071KL,Yageo,RC0603FR-071KL,RCHIP-1K-0603,Resistor_SMD:R_0603_1608Metric_Pad0.98x0.95mm_HandSolder,OK,Device:R_Small,OK,"value is a variable ref, not flattened"
SW1,KSC741J LFS,,Tactile SPST,KSC741JLFS,ITT C&K,,,,MISSING,Switch:SW_Push,OK,footprint missing ((none))
SW2,KSC741J LFS,,Tactile SPST,KSC741JLFS,ITT C&K,,,,MISSING,Switch:SW_Push,OK,footprint missing ((none))
SW3,TL3301AF160QJ,,Tactile SPST (discharge),TL3301AF160QJ,E-Switch,,,,MISSING,Switch:SW_Push,OK,footprint missing ((none))
T1,ATB322524,,1:10 HV pulse xfmr,ATB322524-0110-T000,TDK,ATB322524,ATB322524_PROTO,ATB322524,UNRESOLVABLE,NewAE_AltiumLib:root_0_xformer_2_2_hv_NewAE_AltiumLib.DBLib,UNRESOLVABLE,footprint unresolvable ((no lib prefix)); symbol lib unresolvable (NewAE_AltiumLib:root_0_xformer_2_2_hv_NewAE_AltiumLib.DBLib)
T2,ATB322524,,1:10 HV pulse xfmr,ATB322524-0110-T000,TDK,ATB322524,ATB322524_PROTO,ATB322524,UNRESOLVABLE,NewAE_AltiumLib:root_0_xformer_2_2_hv_NewAE_AltiumLib.DBLib,UNRESOLVABLE,footprint unresolvable ((no lib prefix)); symbol lib unresolvable (NewAE_AltiumLib:root_0_xformer_2_2_hv_NewAE_AltiumLib.DBLib)
U1,SC0915,*,RPi Pico module,SC0915,Raspberry Pi,,SC0915,Module:RaspberryPi_Pico_SMD,OK,MCU_Module:RaspberryPi_Pico_Extensive,OK,

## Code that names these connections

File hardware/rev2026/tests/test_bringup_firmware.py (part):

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
# bringup.py constant name -> net-name fragment its GPIO must land on.
#
# PIN_HV_DET_LED is deliberately absent. D6 was firmware-driven off GP6 until
# Q5 (P-FET, gate on CHARGED) took it over in hardware, so there is no GPIO to
# assert against and GP6 is free.
BRINGUP_PINS = {
    'PIN_STATUS_LED': 'STATUS_LED',
    'PIN_CHARGE_LED': 'CHARGE_LED',
    'PIN_SAFE_LED': 'SAFE_LED_DRV',
    'PIN_ARM_SW': 'ARM_SW',
    'PIN_PULSE_SW': 'PULSE_SW',
    'PIN_SAFE_SW': 'SAFE_SW',
    'PIN_CHARGED': 'CHARGED',
}

# trigtest.py constant name -> net-name fragment its GPIO must land on.
# GP0 is the buffer's output and GP1 is the loopback source the operator
# jumpers to TRIG_IN; both nets are named after the GPIO, so the fragment
# is the GPIO name itself.
TRIGTEST_PINS = {
    'PIN_TRIG': 'GP0',
    'PIN_LOOP_SRC': 'GP1',
    'PIN_STATUS_LED': 'STATUS_LED',
}

# GPIOs that must never appear in a script that claims it cannot make HV.
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
def test_chargetest_pin_map_matches_netlist(node_to_net):
    """chargetest.py's own pin constants land on the right nets."""
    # PIN_HV_DET_LED is gone: Q5 drives D6 from CHARGED in hardware, so
    # chargetest no longer touches a GPIO for it. See BRINGUP_PINS above.
    expected = {
        'PIN_HVPWM': 'HVPWM',
        'PIN_CHARGED': 'CHARGED',
    }
    consts = _constants(CHARGETEST)
    for name, fragment in expected.items():
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    3.20 V once GP26 was configured, confirming no charge was present.
    """
    consts = _constants(script)
    if 'PIN_CHARGED' not in consts:
        pytest.skip(f'{script.name} does not read CHARGED')
    assert 'PIN_CHARGED_ADC' in consts, \
        (f'{script.name} reads CHARGED on GP18 but never configures GP26, the '
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def test_charged_pads_are_on_one_net(node_to_net, script):
    """Both configured pads really are the same net on this board."""
    consts = _constants(script)
    if 'PIN_CHARGED' not in consts:
        pytest.skip(f'{script.name} does not read CHARGED')
    nets = set()
    for name in ('PIN_CHARGED', 'PIN_CHARGED_ADC'):
        gpio = consts[name]
        node = f'U1.{GPIO_TO_PAD[gpio]}'
        assert node in node_to_net, f'{name} = GP{gpio} ({node}) is not connected'
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

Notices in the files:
parts and their libraries:
PRJLICENSE: CC BY-SA 3.0
